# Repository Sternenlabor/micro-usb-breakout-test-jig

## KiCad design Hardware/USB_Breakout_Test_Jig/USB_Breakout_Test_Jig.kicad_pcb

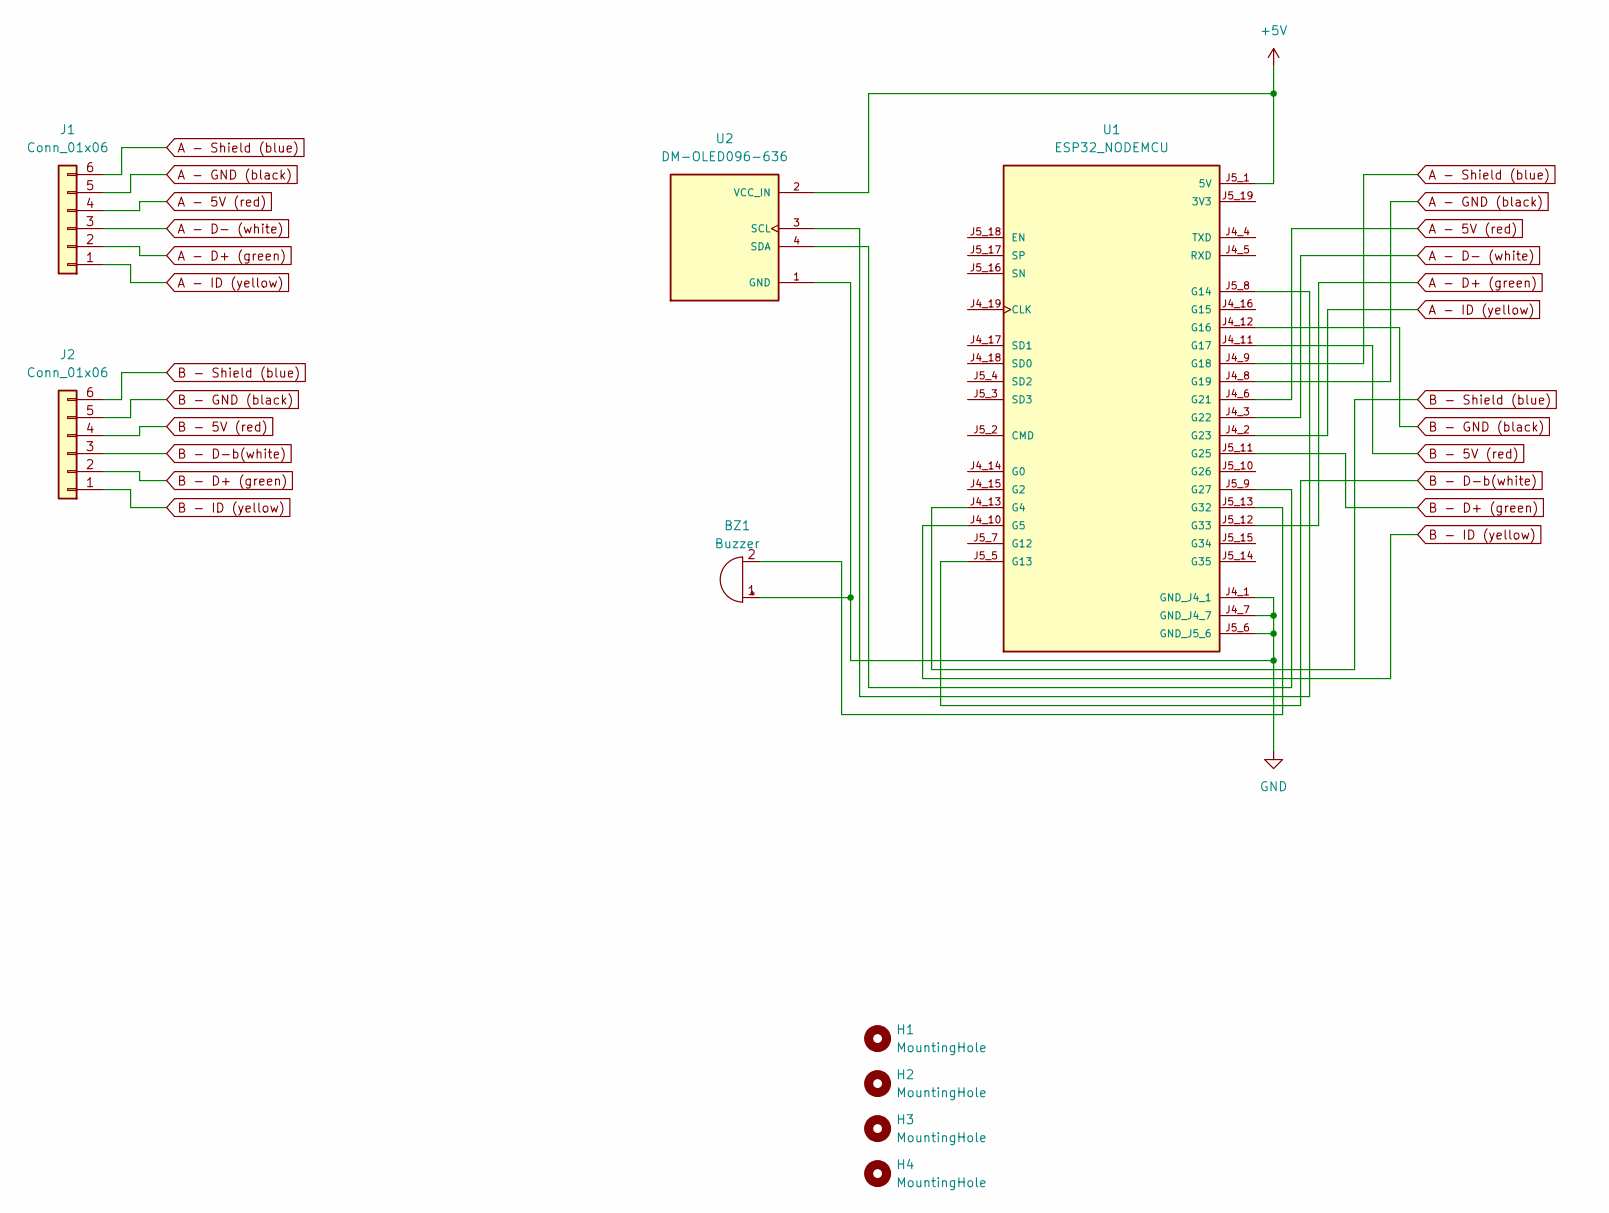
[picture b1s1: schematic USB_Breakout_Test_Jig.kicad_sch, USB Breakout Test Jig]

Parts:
BZ1: Buzzer; Buzzer_12x9.5RM7.6
H1, H2, H3, H4: MountingHole; MountingHole_3.2mm_M3
J1, J2: Conn_01x06; JST_XH_S6B-XH-A_1x06_P2.50mm_Horizontal
U1: ESP32_NODEMCU; MODULE_ESP32_NODEMCU
U2: DM-OLED096-636; MODULE_DM-OLED096-636; PARTREV 2018-09-10

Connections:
+5V: U1.J5_1 (5V), U2.2 (VCC_IN)
A - 5V (red): J1.4, U1.J4_6 (G21)
A - D+ (green): J1.2, U1.J5_12 (G33)
A - D- (white): J1.3, U1.J4_3 (G22)
A - GND (black): J1.5, U1.J4_8 (G19)
A - ID (yellow): J1.1, U1.J4_2 (G23)
A - Shield (blue): J1.6, U1.J4_9 (G18)
B - 5V (red): J2.4, U1.J4_11 (G17)
B - D+ (green): J2.2, U1.J5_11 (G25)
B - D-b(white): J2.3, U1.J5_5 (G13)
B - GND (black): J2.5, U1.J4_12 (G16)
B - ID (yellow): J2.1, U1.J4_10 (G5)
B - Shield (blue): J2.6, U1.J4_13 (G4)
GND: BZ1.1 (-), U1.J4_1 (GND_J4_1), U1.J4_7 (GND_J4_7), U1.J5_6 (GND_J5_6), U2.1 (GND)
unnamed: BZ1.2 (+), U1.J5_13 (G32)
unnamed: U1.J5_8 (G14), U2.3 (SCL)
unnamed: U1.J5_9 (G27), U2.4 (SDA)

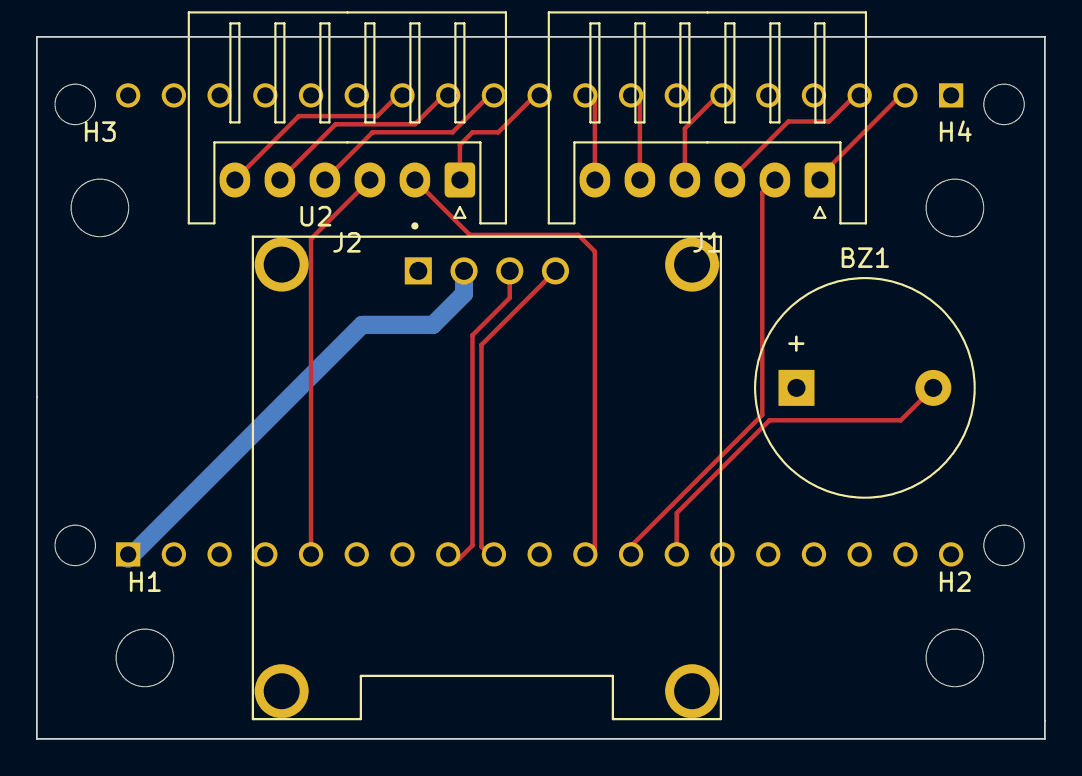
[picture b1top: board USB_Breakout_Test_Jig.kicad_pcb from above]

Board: 2 copper layers, 56.0 x 39.0 mm, 9 parts (1 on the bottom side), 17 nets.

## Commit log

2024-02-15 ༼ つ ◕_◕ ༽つ initial commit
2024-03-11 v1.0
